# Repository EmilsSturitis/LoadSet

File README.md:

# LoadSet

Programmable Load 
Based on https://github.com/bertrik/ElectronicLoad

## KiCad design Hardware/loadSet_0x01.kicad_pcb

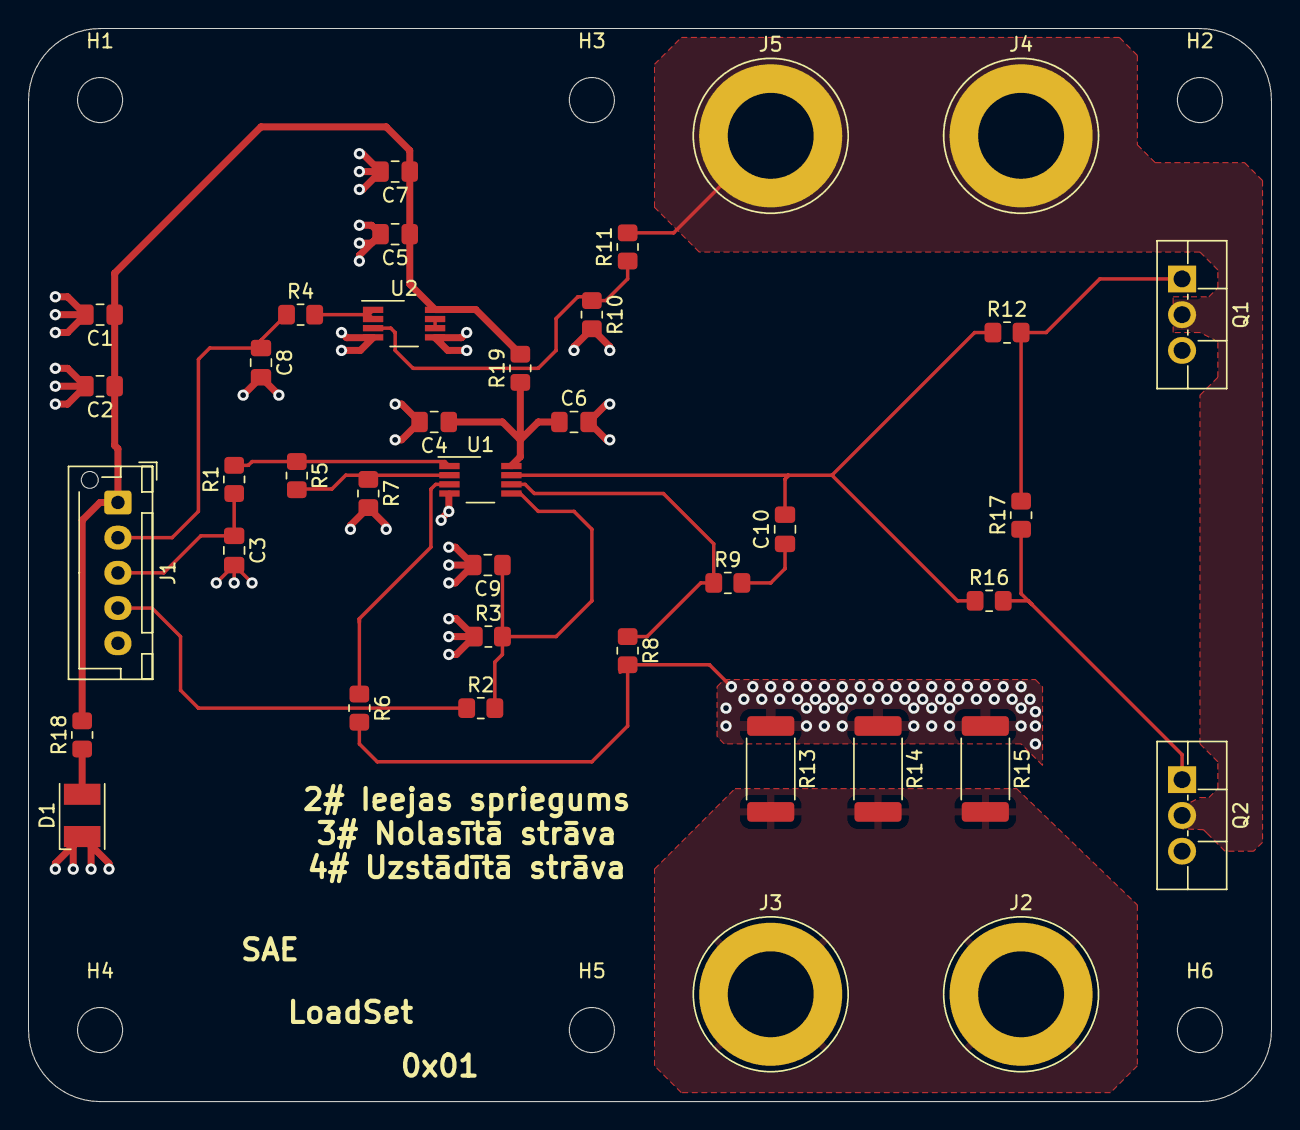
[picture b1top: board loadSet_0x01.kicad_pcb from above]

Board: 2 copper layers, 88.3 x 76.2 mm, 45 parts (0 on the bottom side), 20 nets.

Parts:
C1, C2, C4, C5, C6, C7: C_Small; C_0805_2012Metric_Pad1.18x1.45mm_HandSolder
C3, C8: 1u; C_0805_2012Metric_Pad1.18x1.45mm_HandSolder
C9: 100n; C_0805_2012Metric_Pad1.18x1.45mm_HandSolder
C10: 22n; C_0805_2012Metric_Pad1.18x1.45mm_HandSolder
D1: LED; LED_PLCC-2
H1, H2, H3, H4, H5, H6: MountingHole; MountingHole_3.2mm_M3
J1: Conn_01x05; JST_XH_B5B-XH-AM_1x05_P2.50mm_Vertical
J2, J3, J4, J5: Conn_01x01; Banana_Jack_1Pin
Q1, Q2: Q_NMOS_GDS; TO-220F-3_Vertical
R1, R4, R12, R16, R17, R18: 150; R_0805_2012Metric_Pad1.20x1.40mm_HandSolder
R2, R5, R8, R10: 20k; R_0805_2012Metric_Pad1.20x1.40mm_HandSolder
R3, R6, R7: 3k6; R_0805_2012Metric_Pad1.20x1.40mm_HandSolder
R9: 2k2; R_0805_2012Metric_Pad1.20x1.40mm_HandSolder
R11: 100k; R_0805_2012Metric_Pad1.20x1.40mm_HandSolder
R13, R14, R15: 0.3; R_2512_6332Metric_Pad1.40x3.35mm_HandSolder
R19: 0; R_0805_2012Metric_Pad1.20x1.40mm_HandSolder
U1, U2: OPA2333xxDGK; VSSOP-8_3.0x3.0mm_P0.65mm

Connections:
+5V: C1.1, C2.1, C4.1, C5.1, C6.1, C7.1, J1.1, R18.2, R19.1, R19.2, U1.8, U2.8
/+Load: J4.1, J5.1, Q1.2, Q2.2, R11.2
/Iread: C3.1, J1.3, R1.1
/SetCurr: J1.4, R2.1
/Vread: C8.1, J1.2, R4.1
GND: C1.2, C2.2, C3.2, C4.2, C5.2, C6.2, C7.2, C8.2, C9.2, D1.1, J1.5, J2.1, J3.1, R3.1, R7.2, R10.2, R13.2, R14.2, R15.2, U1.4, U2.4, U2.5
unnamed: C9.1, R2.2, R3.2, U1.5
unnamed: C10.1, R9.2
unnamed: C10.2, R12.1, R16.1, U1.7
unnamed: D1.2, R18.1
unnamed: Q1.1, R12.2, R17.2
unnamed: Q1.3, Q2.3, R6.2, R8.2, R13.1, R14.1, R15.1
unnamed: Q2.1, R16.2, R17.1
unnamed: R1.2, R5.1, U1.1
unnamed: R4.2, U2.1, U2.2
unnamed: R5.2, R7.1, U1.2
unnamed: R6.1, U1.3
unnamed: R8.1, R9.1, U1.6
unnamed: R10.1, R11.1, U2.3
unnamed: U2.6, U2.7

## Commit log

2023-01-21 updated project structure
2024-04-01 additional code and values
